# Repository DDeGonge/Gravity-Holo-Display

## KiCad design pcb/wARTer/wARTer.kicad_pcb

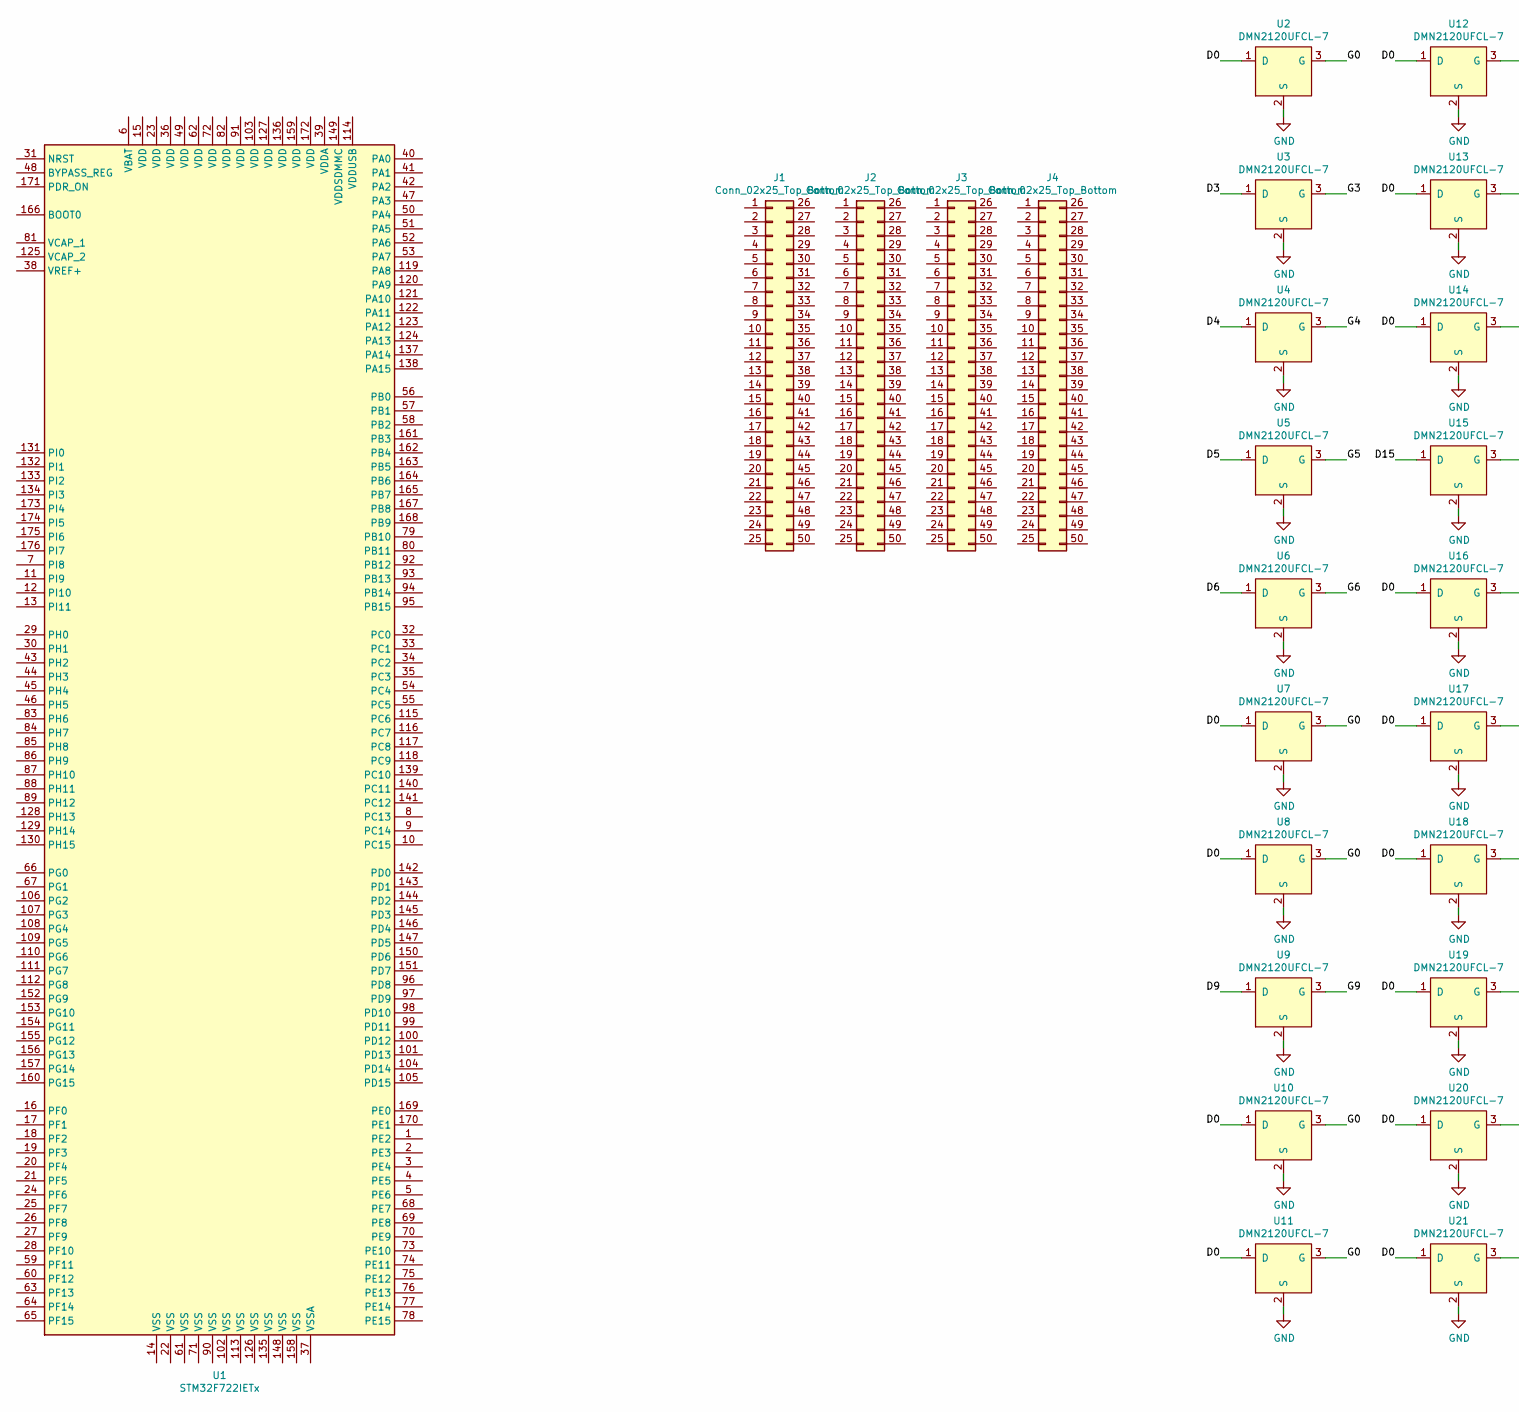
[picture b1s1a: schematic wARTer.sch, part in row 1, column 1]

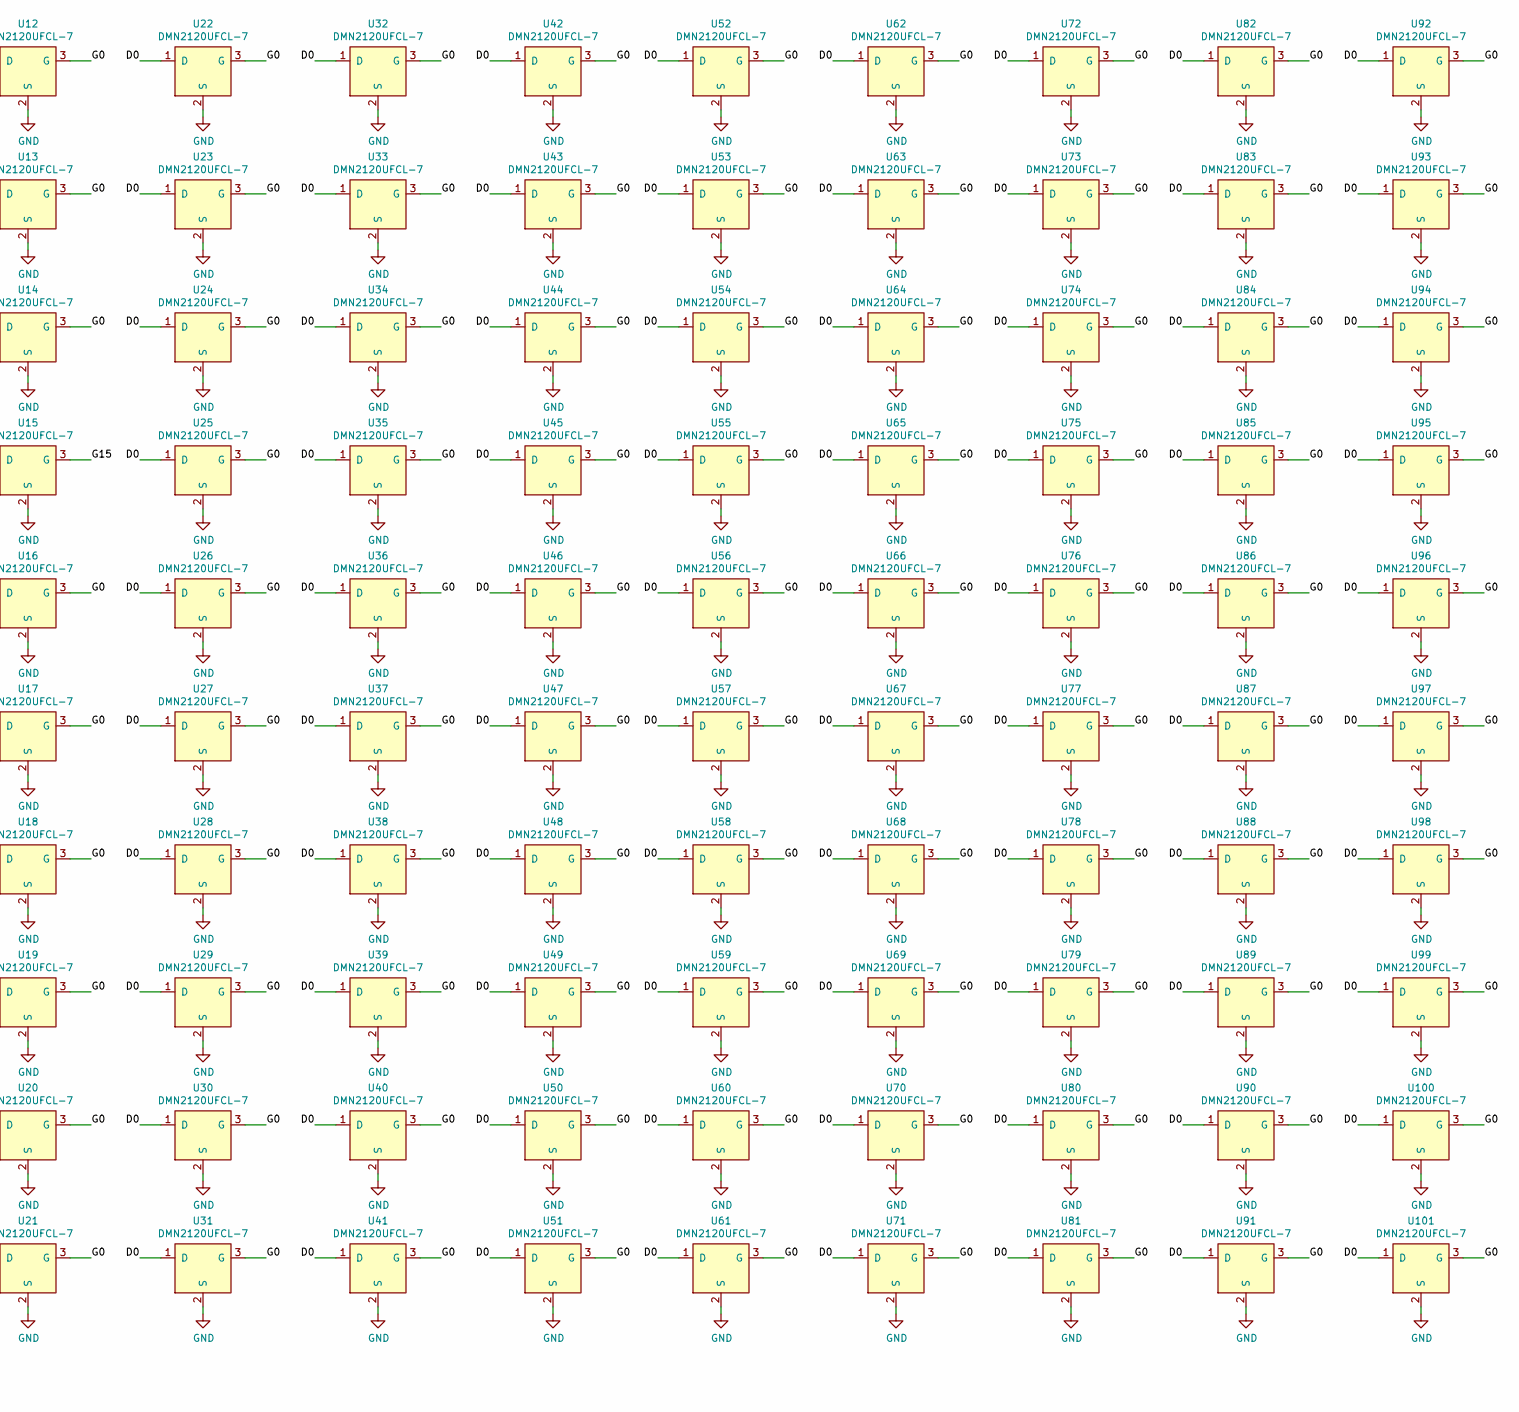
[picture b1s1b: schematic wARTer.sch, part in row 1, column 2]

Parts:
J1: Conn_02x25_Top_Bottom; PinHeader_2x05_P2.54mm_Vertical_SMD
J2, J3, J4: Conn_02x25_Top_Bottom; PinHeader_2x25_P2.54mm_Vertical_SMD
U1: STM32F722IETx; LQFP-176_24x24mm_P0.5mm
U2, U3, U4, U5, U6, U7, U8, U9, U10, U11, U12, U13, U14, U15, U16, U17, U18, U19, U20, U21, U22, U23, U24, U25, U26, U27, U28, U29, U30, U31, U32, U33, U34, U35, U36, U37, U38, U39, U40, U41, U42, U43, U44, U45, U46, U47, U48, U49, U50, U51, U52, U53, U54, U55, U56, U57, U58, U59, U60, U61, U62, U63, U64, U65, U66, U67, U68, U69, U70, U71, U72, U73, U74, U75, U76, U77, U78, U79, U80, U81, U82, U83, U84, U85, U86, U87, U88, U89, U90, U91, U92, U93, U94, U95, U96, U97, U98, U99, U100, U101: DMN2120UFCL-7; U-DFN1616-6

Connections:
/D0: U2.1 (D), U7.1 (D), U8.1 (D), U10.1 (D), U11.1 (D), U12.1 (D), U13.1 (D), U14.1 (D), U16.1 (D), U17.1 (D), U18.1 (D), U19.1 (D), U20.1 (D), U21.1 (D), U22.1 (D), U23.1 (D), U24.1 (D), U25.1 (D), U26.1 (D), U27.1 (D), U28.1 (D), U29.1 (D), U30.1 (D), U31.1 (D), U32.1 (D), U33.1 (D), U34.1 (D), U35.1 (D), U36.1 (D), U37.1 (D), U38.1 (D), U39.1 (D), U40.1 (D), U41.1 (D), U42.1 (D), U43.1 (D), U44.1 (D), U45.1 (D), U46.1 (D), U47.1 (D), U48.1 (D), U49.1 (D), U50.1 (D), U51.1 (D), U52.1 (D), U53.1 (D), U54.1 (D), U55.1 (D), U56.1 (D), U57.1 (D), U58.1 (D), U59.1 (D), U60.1 (D), U61.1 (D), U62.1 (D), U63.1 (D), U64.1 (D), U65.1 (D), U66.1 (D), U67.1 (D), U68.1 (D), U69.1 (D), U70.1 (D), U71.1 (D), U72.1 (D), U73.1 (D), U74.1 (D), U75.1 (D), U76.1 (D), U77.1 (D), U78.1 (D), U79.1 (D), U80.1 (D), U81.1 (D), U82.1 (D), U83.1 (D), U84.1 (D), U85.1 (D), U86.1 (D), U87.1 (D), U88.1 (D), U89.1 (D), U90.1 (D), U91.1 (D), U92.1 (D), U93.1 (D), U94.1 (D), U95.1 (D), U96.1 (D), U97.1 (D), U98.1 (D), U99.1 (D), U100.1 (D), U101.1 (D)
/D3: U3.1 (D)
/D4: U4.1 (D)
/D5: U5.1 (D)
/D6: U6.1 (D)
/D9: U9.1 (D)
/D15: U15.1 (D)
/G0: U2.3 (G), U7.3 (G), U8.3 (G), U10.3 (G), U11.3 (G), U12.3 (G), U13.3 (G), U14.3 (G), U16.3 (G), U17.3 (G), U18.3 (G), U19.3 (G), U20.3 (G), U21.3 (G), U22.3 (G), U23.3 (G), U24.3 (G), U25.3 (G), U26.3 (G), U27.3 (G), U28.3 (G), U29.3 (G), U30.3 (G), U31.3 (G), U32.3 (G), U33.3 (G), U34.3 (G), U35.3 (G), U36.3 (G), U37.3 (G), U38.3 (G), U39.3 (G), U40.3 (G), U41.3 (G), U42.3 (G), U43.3 (G), U44.3 (G), U45.3 (G), U46.3 (G), U47.3 (G), U48.3 (G), U49.3 (G), U50.3 (G), U51.3 (G), U52.3 (G), U53.3 (G), U54.3 (G), U55.3 (G), U56.3 (G), U57.3 (G), U58.3 (G), U59.3 (G), U60.3 (G), U61.3 (G), U62.3 (G), U63.3 (G), U64.3 (G), U65.3 (G), U66.3 (G), U67.3 (G), U68.3 (G), U69.3 (G), U70.3 (G), U71.3 (G), U72.3 (G), U73.3 (G), U74.3 (G), U75.3 (G), U76.3 (G), U77.3 (G), U78.3 (G), U79.3 (G), U80.3 (G), U81.3 (G), U82.3 (G), U83.3 (G), U84.3 (G), U85.3 (G), U86.3 (G), U87.3 (G), U88.3 (G), U89.3 (G), U90.3 (G), U91.3 (G), U92.3 (G), U93.3 (G), U94.3 (G), U95.3 (G), U96.3 (G), U97.3 (G), U98.3 (G), U99.3 (G), U100.3 (G), U101.3 (G)
/G3: U3.3 (G)
/G4: U4.3 (G)
/G5: U5.3 (G)
/G6: U6.3 (G)
/G9: U9.3 (G)
/G15: U15.3 (G)
GND: U2.2 (S), U3.2 (S), U4.2 (S), U5.2 (S), U6.2 (S), U7.2 (S), U8.2 (S), U9.2 (S), U10.2 (S), U11.2 (S), U12.2 (S), U13.2 (S), U14.2 (S), U15.2 (S), U16.2 (S), U17.2 (S), U18.2 (S), U19.2 (S), U20.2 (S), U21.2 (S), U22.2 (S), U23.2 (S), U24.2 (S), U25.2 (S), U26.2 (S), U27.2 (S), U28.2 (S), U29.2 (S), U30.2 (S), U31.2 (S), U32.2 (S), U33.2 (S), U34.2 (S), U35.2 (S), U36.2 (S), U37.2 (S), U38.2 (S), U39.2 (S), U40.2 (S), U41.2 (S), U42.2 (S), U43.2 (S), U44.2 (S), U45.2 (S), U46.2 (S), U47.2 (S), U48.2 (S), U49.2 (S), U50.2 (S), U51.2 (S), U52.2 (S), U53.2 (S), U54.2 (S), U55.2 (S), U56.2 (S), U57.2 (S), U58.2 (S), U59.2 (S), U60.2 (S), U61.2 (S), U62.2 (S), U63.2 (S), U64.2 (S), U65.2 (S), U66.2 (S), U67.2 (S), U68.2 (S), U69.2 (S), U70.2 (S), U71.2 (S), U72.2 (S), U73.2 (S), U74.2 (S), U75.2 (S), U76.2 (S), U77.2 (S), U78.2 (S), U79.2 (S), U80.2 (S), U81.2 (S), U82.2 (S), U83.2 (S), U84.2 (S), U85.2 (S), U86.2 (S), U87.2 (S), U88.2 (S), U89.2 (S), U90.2 (S), U91.2 (S), U92.2 (S), U93.2 (S), U94.2 (S), U95.2 (S), U96.2 (S), U97.2 (S), U98.2 (S), U99.2 (S), U100.2 (S), U101.2 (S)

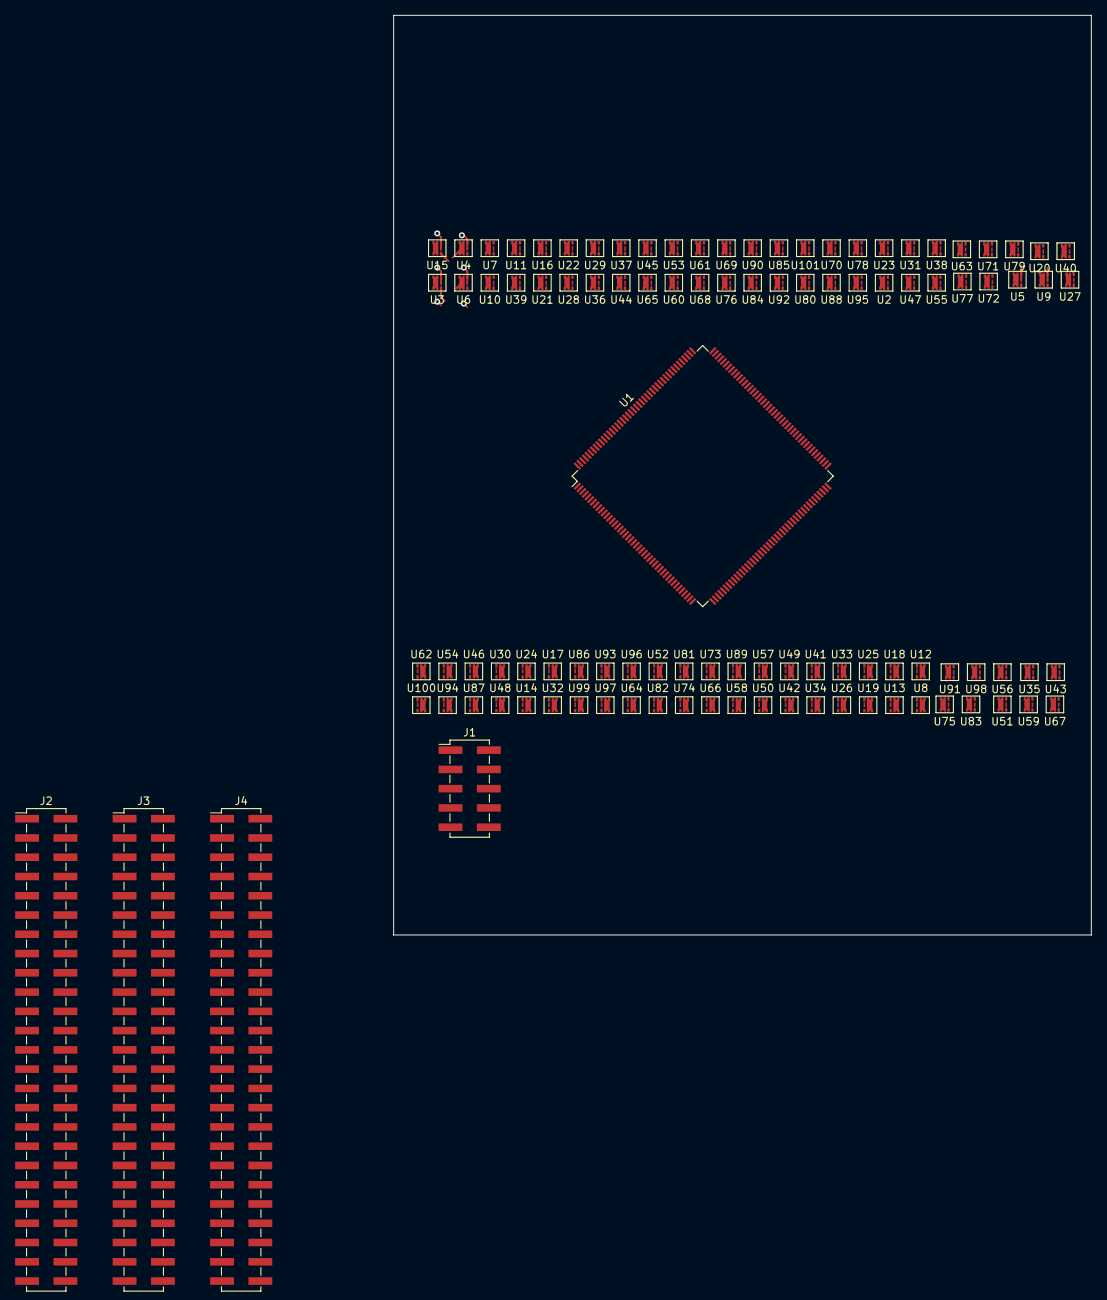
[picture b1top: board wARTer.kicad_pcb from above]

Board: 2 copper layers, 92.0 x 121.2 mm, 105 parts (0 on the bottom side), 3 nets.

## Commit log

2020-10-10 inital commit
2021-10-16 I forgot to push sooner, sorry :)
